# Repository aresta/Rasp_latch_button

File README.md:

# Raspberry Pi Power Button HAT - Power On, Shutdown and Power off

### Mini HAT with a Push Button to **Power** the Raspberry Pi **On** and **Off** Safely, After the Shutdown Completes.

- When the Raspberry Pi is **off**, a button press powers it on.
- When the Raspberry Pi is **on**, a button press initiates the shutdown sequence, and when it completes, cuts the power automatically.
- An additional switch in the USB cable is not necessary; after the shutdown, the power is completely off.

Only shutdown sometimes is not enough. After the shutdown the Raspberry Pi enters a halted state, the operating system has ceased all activity, but the hardware remains powered. Most models continue to draw power (up to 1.5W for a Pi 4). The red Power LED often remains lit, and some peripherals, like a DSI display, can remain powered with the backlight active. In those cases is better to cut the power completely.

This little board is useful for home devices, like audio players or home theater systems, to avoid having to initiate the shutdown in the user interface, wait some time, and then cut off the power manually.

If you initiate the shutdown from the device user interface it works the same, after the shutdown sequence, it will cut the power.

## The Mini HAT:

- **USB-C power connector**. Use only this connector to power the Raspberry Pi.
- **Push button**. A push button of any size or type.
- **5x2 socket** to plug into the Raspberry Pi header. It provides access to GPIO2, GPIO3, and power pins. 

## GPIO pins and Overlays:
You have to configure **GPIO 2 and 3** in the config.txt file. For power management, we specifically use these two specialized **overlays**:

- **gpio-shutdown**:
  - What it does: Configures a GPIO pin to act like a keyboard's power button.
  - The Result: When the pin is triggered, it sends a KEY_POWER event to the system, which tells systemd to perform a clean, safe shutdown. It is much safer than simply pulling the power plug.
    
- **gpio-poweroff**:
  - What it does: Reaches out to the "outside world" after the Pi has finished its shutdown process.
  - The Result: Once the Pi's software is completely halted, it flips the state of a GPIO pin. This is intended to signal an external circuit (like our HAT) that it is now safe to physically cut the electricity to the Pi. 

### GPIO 2: Shutdown (gpio-shutdown) 
- Add ***dtoverlay=gpio-shutdown*** to your config file to enable GPIO 2 as the shutdown trigger.
- Configuration: Add this line to your config file:    
    ``dtoverlay=gpio-shutdown,gpio_pin=2,active_low=1,gpio_pull=up``

### GPIO 3: Power-Off Signaling (gpio-poweroff)
- Add ***dtoverlay=gpio-poweroff*** to your config file to enable GPIO 3 as the poweroff trigger.
- The pin will transition to its active state (LOW) only after the kernel has finished shutting down, ensuring no SD card corruption occurs 
- active_low=1: The pin is HIGH (3.3V) while the Pi is running and transitions to LOW (0V) once it is safe to cut power
- Configuration: Add this line to your config file:    
    ``dtoverlay=gpio-poweroff,gpiopin=3,active_low=1``

For example:

```bash
[all]
# Add your shutdown/poweroff overlays here
dtoverlay=gpio-shutdown,gpio_pin=2,active_low=1,gpio_pull=up
dtoverlay=gpio-poweroff,gpiopin=3,active_low=1
```

### Config file Location
Configure the behaviour of the GPIO pins in the Raspberry Pi config file:

- Raspberry Pi OS Bookworm (and newer): The file is located at /boot/firmware/config.txt.
- Older OS Versions (Bullseye and earlier): The file is located at /boot/config.txt.
- On another computer: If you insert the SD card into a PC or Mac, the file is located in the root directory of the small partition named boot or bootfs.

## The circuit 
Basic power latch circuit combined with the ***shutdown*** and ***poweroff*** GPIO's to manage the power off sequence.

- Before the button is pressed Q1 is off because R1 keeps the gate at the same voltage than the source. There is no power at the 5V pin.
- When the button is pressed, it brings the gate of Q1 to GND, activating the power. C1 prevents button bouncing.
- When the Rasperry Pi boots it keeps the GPIO 3 (power_off pin) up, keeping Q2 on, what keeps Q1 also on.
- When the Rasperry Pi is on and the button is pressed again, it sends a LOW signal to the GPIO 2 (sht_dwn pin), what initiates the shut down sequence.
- When shut down sequence completes, the GPIO 3 (power_off pin) goes LOW, what switchs Q2 off, and therefor Q1 switchs off also, and the power gets cut off.

## Restrictions
- The maximum current that the board can handle is about 7A, but the maximum that you can get from this USB-C connector is 3A (15W).  It should be enough for most applications with few basic peripherals.
- The HAT takes the first 10 pins of the header, to use two 5V and two GND pins, and also for stability.  It means that the pins of GPIO's 2,3,4,14,15 are not available in the header for other uses.
- Conflict with I2C: Because Pin 5 (GPIO 3) is the only pin that can wake the Pi from a deep sleep, using it for a shutdown button will conflict with I2C devices.
- There are no power or USB protections in the PCB. **Use at your own risk!**

## Compatibility with Raspberry Pi Versions
The overlays used for shutdown and power-off are supported on almost all models, provided you are using a modern operating system (Raspbian Stretch 2017 or newer). 

- **Raspberry Pi 4 & 5**: Fully compatible. Note that while the physical pinout is identical, the Raspberry Pi 5 uses a new RP1 chip for I/O; however, the kernel handles these device tree overlays so they function the same way as on older boards.
- **Raspberry Pi 2, 3, Zero, and B+**: Fully compatible with the standard 40-pin header.
- **Original Raspberry Pi 1**: Probably not compatible without modifications. On these specific early models, GPIO 1 is used for shutdown instead of the modern standard GPIO 3

Anyway, I have only tested it with a Raspberry Pi 4b.

### There are no power or USB protections in the PCB. **Use at your own risk!**

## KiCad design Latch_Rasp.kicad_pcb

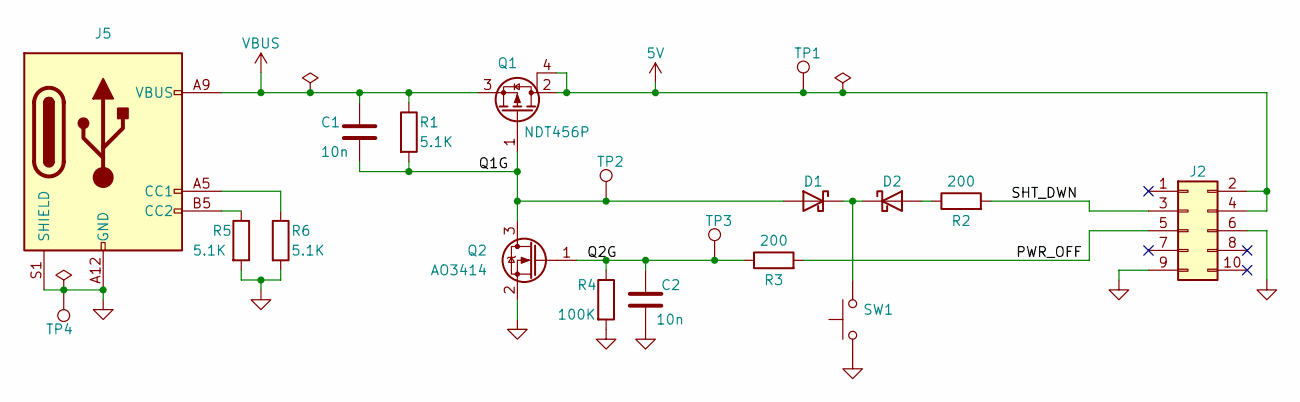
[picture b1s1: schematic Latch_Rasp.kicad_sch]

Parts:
C1, C2: 10n; C_0805_2012Metric
D1, D2: D_Schottky; D_1206_3216Metric
J2: Conn_02x03_Counter_Clockwise; PinSocket_2x05_P2.54mm_Vertical
J5: USB_C_Receptacle_PowerOnly_6P; USB_C_Receptacle_GCT_USB4125-xx-x-0190_6P_TopMnt_Horizontal
Q1: NDT456P; SOT-223
Q2: AO3414; SOT-23
R1, R5, R6: 5.1K; R_0805_2012Metric
R2, R3: 200; R_0805_2012Metric
R4: 100K; R_0805_2012Metric
SW1: SW_Push; PinHeader_1x02_P2.54mm_Vertical
TP1: 5V; TestPoint_Pad_D1.0mm
TP2: Q1G; TestPoint_Pad_D1.0mm
TP3: Q2G; TestPoint_Pad_D1.0mm
TP4: gnd; TestPoint_Pad_D1.0mm

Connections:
5V: J2.2, J2.4, Q1.2 (D), Q1.4 (D), TP1.1
/PWR_OFF: J2.5, R3.2
/Q1G: C1.2, D1.2 (A), Q1.1 (G), Q2.3 (D), R1.2, TP2.1
/Q2G: C2.1, Q2.1 (G), R3.1, R4.1, TP3.1
/SHT_DWN: J2.3, R2.2
GND: C2.2, J2.6, J2.9, J5.A12 (GND), J5.B12 (GND), J5.S1 (SHIELD), Q2.2 (S), R4.2, R5.2, R6.2, SW1.1, TP4.1
unnamed: D1.1 (K), D2.1 (K), SW1.2
unnamed: D2.2 (A), R2.1
unnamed: J5.A5 (CC1), R6.1
unnamed: J5.B5 (CC2), R5.1
VBUS: C1.1, J5.A9 (VBUS), J5.B9 (VBUS), Q1.3 (S), R1.1

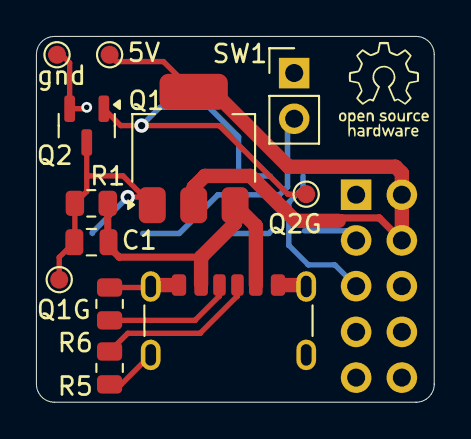
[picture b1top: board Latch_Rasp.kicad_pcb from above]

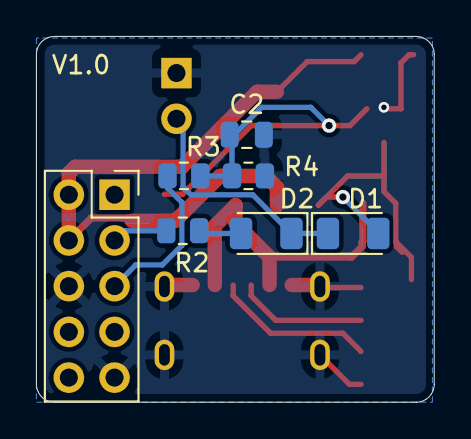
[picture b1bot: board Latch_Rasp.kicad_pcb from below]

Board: 2 copper layers, 22.1 x 20.3 mm, 19 parts (7 on the bottom side), 11 nets.

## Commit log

2026-01-18 Clarify shutdown sequence description in README
    Removed redundant wording for clarity.
2026-01-19 Update current handling information in README
